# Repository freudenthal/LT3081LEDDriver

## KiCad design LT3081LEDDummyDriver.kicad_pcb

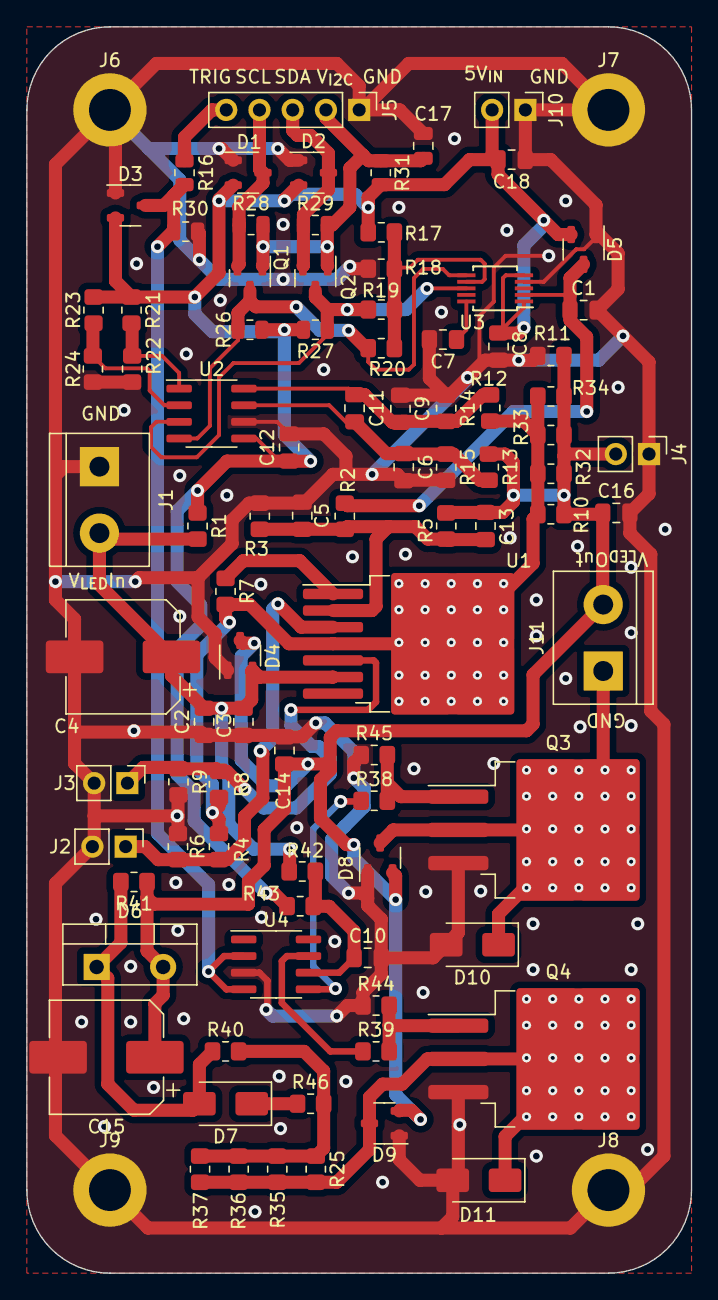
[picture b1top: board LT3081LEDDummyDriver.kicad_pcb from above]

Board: 2 copper layers, 50.8 x 95.2 mm, 94 parts (0 on the bottom side), 33 nets.

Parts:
C1, C5, C13: 10nF; C_0805_2012Metric_Pad1.18x1.45mm_HandSolder
C2, C14, C18: 10uF; C_0805_2012Metric_Pad1.18x1.45mm_HandSolder
C3, C6, C7, C8, C9, C10, C11, C12, C16: 1uF; C_0805_2012Metric_Pad1.18x1.45mm_HandSolder
C4, C15: 100uF; CP_Elec_8x10.5
C17: 1uF; C_0805_2012Metric
D1, D2, D3, D4, D5, D8, D9: 100V; SOT-23-3
D6: PSDP08120S1; TO-220-2_Vertical
D7, D10, D11: 2A; D_SMA
J1: V_{IN}; TerminalBlock_bornier-2_P5.08mm
J2: PosIMon; PinHeader_1x02_P2.54mm_Vertical
J3: PosTempMon; PinHeader_1x02_P2.54mm_Vertical
J4: V_{LED}; PinHeader_1x02_P2.54mm_Vertical
J5: I2C; PinHeader_1x05_P2.54mm_Vertical
J6, J7, J8, J9: Screw_Terminal_01x01; MountingHole_3.2mm_M3_DIN965_Pad
J10: +5V_{IN}; PinHeader_1x02_P2.54mm_Vertical
J11: LED; TerminalBlock_bornier-2_P5.08mm
Q1, Q2: Q_NMOS_GSD; SOT-23
Q3, Q4: IXTA80N075L2; TO-263-3_TabPin2
R1: NSΩ; R_0805_2012Metric_Pad1.20x1.40mm_HandSolder
R2, R3, R4, R6, R7, R8, R9, R11, R12, R13, R14, R15, R17, R18, R19, R20, R21, R22, R23, R24: 1kΩ; R_0805_2012Metric_Pad1.20x1.40mm_HandSolder
R5: 4kΩ; R_0805_2012Metric_Pad1.20x1.40mm_HandSolder
R10, R32, R33, R34: 10mΩ; R_0805_2012Metric_Pad1.20x1.40mm_HandSolder
R16: 100Ω; R_0805_2012Metric
R25, R35, R36, R37: 10Ω; R_0805_2012Metric_Pad1.20x1.40mm_HandSolder
R26, R27, R28, R29, R30: 10kΩ; R_0805_2012Metric
R31: NS; R_0805_2012Metric
R38, R39, R42, R43: 0Ω; R_0805_2012Metric_Pad1.20x1.40mm_HandSolder
R40, R41, R46: 100Ω; R_0805_2012Metric_Pad1.20x1.40mm_HandSolder
R44, R45: 100kΩ; R_0805_2012Metric_Pad1.20x1.40mm_HandSolder
U1: LT3081-DPAK-7; TO-263-7_TabPin8
U2: INA219AxD; SOIC-8_3.9x4.9mm_P1.27mm
U3: DACx0501; MSOP-10_3x3mm_P0.5mm
U4: IX4428_SOIC-8; SOIC-8_3.9x4.9mm_P1.27mm

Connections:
+5V: C8.1, C12.1, C18.2, D1.2 (K), D2.2 (K), D3.2 (K), D5.2 (K), J10.2, R1.1, R17.1, R21.1, R23.1, R26.2, R27.2, R31.2, R43.2, U2.5 (VS), U3.1 (V_{DD}), U3.5 (SPI2C)
/DACx0501_DAC/SCL: Q1.3 (D), R20.1, R26.1, U2.4 (SCL), U3.6 (SCL/CLK)
/DACx0501_DAC/SDA: Q2.3 (D), R19.1, R27.1, U2.3 (SDA), U3.8 (SDA/DIN)
/DACx0501_DAC/V_{OUT}: C1.1, D5.3 (A), R2.1, U3.2 (V_{OUT})
/DummyLEDLoad/GATEDGND: D9.3 (A), D11.1 (K), Q4.2 (D), R25.2, R35.2, R36.2, R37.2
/FETSwitch/LEDGND: D8.3 (A), D10.1 (K), J11.1, Q3.2 (D)
/FETSwitch/TRIG: D3.3 (A), R16.2, R30.2, U4.2 (INA), U4.4 (INB)
/FETSwitch/V_{IN}: C2.2, C3.2, C4.1, D4.2 (K), J1.2, R1.2, R42.2, U1.6 (In)
/I2CConnection/VI2C: C17.1, J5.2, Q1.1 (G), Q2.1 (G), R28.2, R29.2, R31.1
/LT3081CurrentSupply/V_{OUT}: R4.1, R7.2, R8.1, R10.1, R12.1, R32.1, R33.1, R34.1, U1.4 (Out), U1.8 (Out)
/V_{LED}: C13.2, C14.1, C15.1, C16.1, D4.3 (A), D6.2 (A), D8.2 (K), D9.2 (K), J4.2, J11.2, R5.2, R10.2, R11.1, R13.1, R32.2, R33.2, R34.2, R41.1
GND: C1.2, C2.1, C3.1, C4.2, C5.2, C6.2, C7.2, C8.2, C9.1, C10.2, C12.2, C14.2, C15.2, C16.2, C17.2, C18.1, D1.1 (K), D2.1 (K), D3.1 (K), D4.1 (K), D5.1 (K), D8.1 (K), D9.1 (K), D10.2 (A), D11.2 (A), J1.1, J2.2, J3.2, J4.1, J5.1, J6.1, J7.1, J8.1, J9.1, J10.1, Q3.3 (S), Q4.3 (S), R3.2, R6.2, R9.2, R11.2, R14.1, R15.2, R18.2, R22.2, R24.2, R30.1, R44.1, R45.1, U2.6 (GND), U3.4 (GND), U4.3 (GND)
unnamed: D1.3 (A), J5.4, Q1.2 (S), R28.1
unnamed: D2.3 (A), J5.3, Q2.2 (S), R29.1
unnamed: D6.1 (K), D7.2 (A), R40.1, R41.2
unnamed: D7.1 (K), R46.1
unnamed: J2.1, R4.2, R6.1, U1.3 (Imon)
unnamed: J3.1, R8.2, R9.1, U1.5 (Temp)
unnamed: J5.5, R16.1
unnamed: Q3.1 (G), R38.2, R45.2
unnamed: Q4.1 (G), R39.2, R44.2
unnamed: R25.1, R35.1, R36.1, R37.1, R40.2, R46.2
unnamed: R7.1, U1.1 (Ilim)
unnamed: C5.1, C13.1, R2.2, R3.1, R5.1, U1.2 (Set)
unnamed: R23.2, R24.1, U2.2 (A0)
unnamed: R21.2, R22.1, U2.1 (A1)
unnamed: C9.2, C11.1, R12.2, R14.2, U2.8 (IN+)
unnamed: C6.1, C11.2, R13.2, R15.1, U2.7 (IN-)
unnamed: R17.2, R18.1, R19.2, R20.2, U3.7 (A0/~CS)
unnamed: C7.1, U3.10 (V_{REF})
unnamed: R38.1, U4.5 (OUTB)
unnamed: C10.1, R42.1, R43.1, U4.6 (V_{CC})
unnamed: R39.1, U4.7 (~OUTA)

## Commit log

2023-09-20 Added output capacitor to allow for smoothing of output voltage spike and an additional protection diode.
2023-11-29 Added extra capacitor and reroute the power to better optimize the board.
